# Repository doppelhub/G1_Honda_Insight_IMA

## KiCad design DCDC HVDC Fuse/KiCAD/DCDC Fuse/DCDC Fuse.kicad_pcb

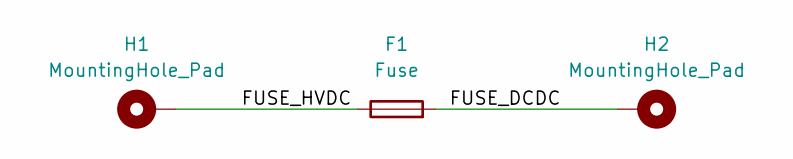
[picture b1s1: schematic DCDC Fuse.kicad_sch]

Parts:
F1: Fuse; Fuseholder_Cylinder-5x20mm_Schurter_0031_8201_Horizontal_Op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
H1, H2: MountingHole_Pad; MountingHole_8.4mm_M8_Pad_TopBottom

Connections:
/FUSE_DCDC: F1.2, H2.1
/FUSE_HVDC: F1.1, H1.1

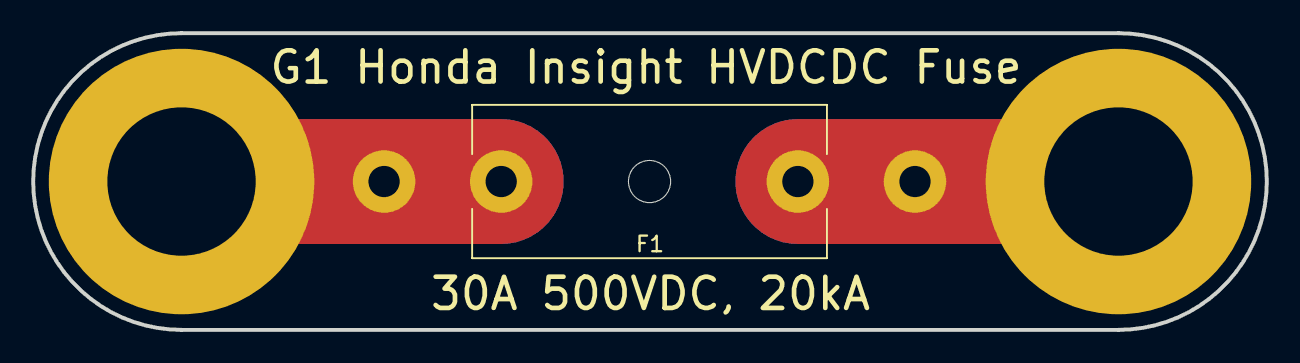
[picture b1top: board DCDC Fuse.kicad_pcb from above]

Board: 2 copper layers, 79.0 x 19.0 mm, 3 parts (0 on the bottom side), 2 nets.

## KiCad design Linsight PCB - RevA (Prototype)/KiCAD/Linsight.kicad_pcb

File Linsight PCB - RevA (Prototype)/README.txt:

THIS IS A PROTOTYPE!!
THIS IS NOT A FINISHED PRODUCT!
DO NOT MAKE THIS PCB AND EXPECT IT TO WORK.

See Folder "RevA Issues" for known issues.

This is a framework ONLY.  Further engineering effort required.

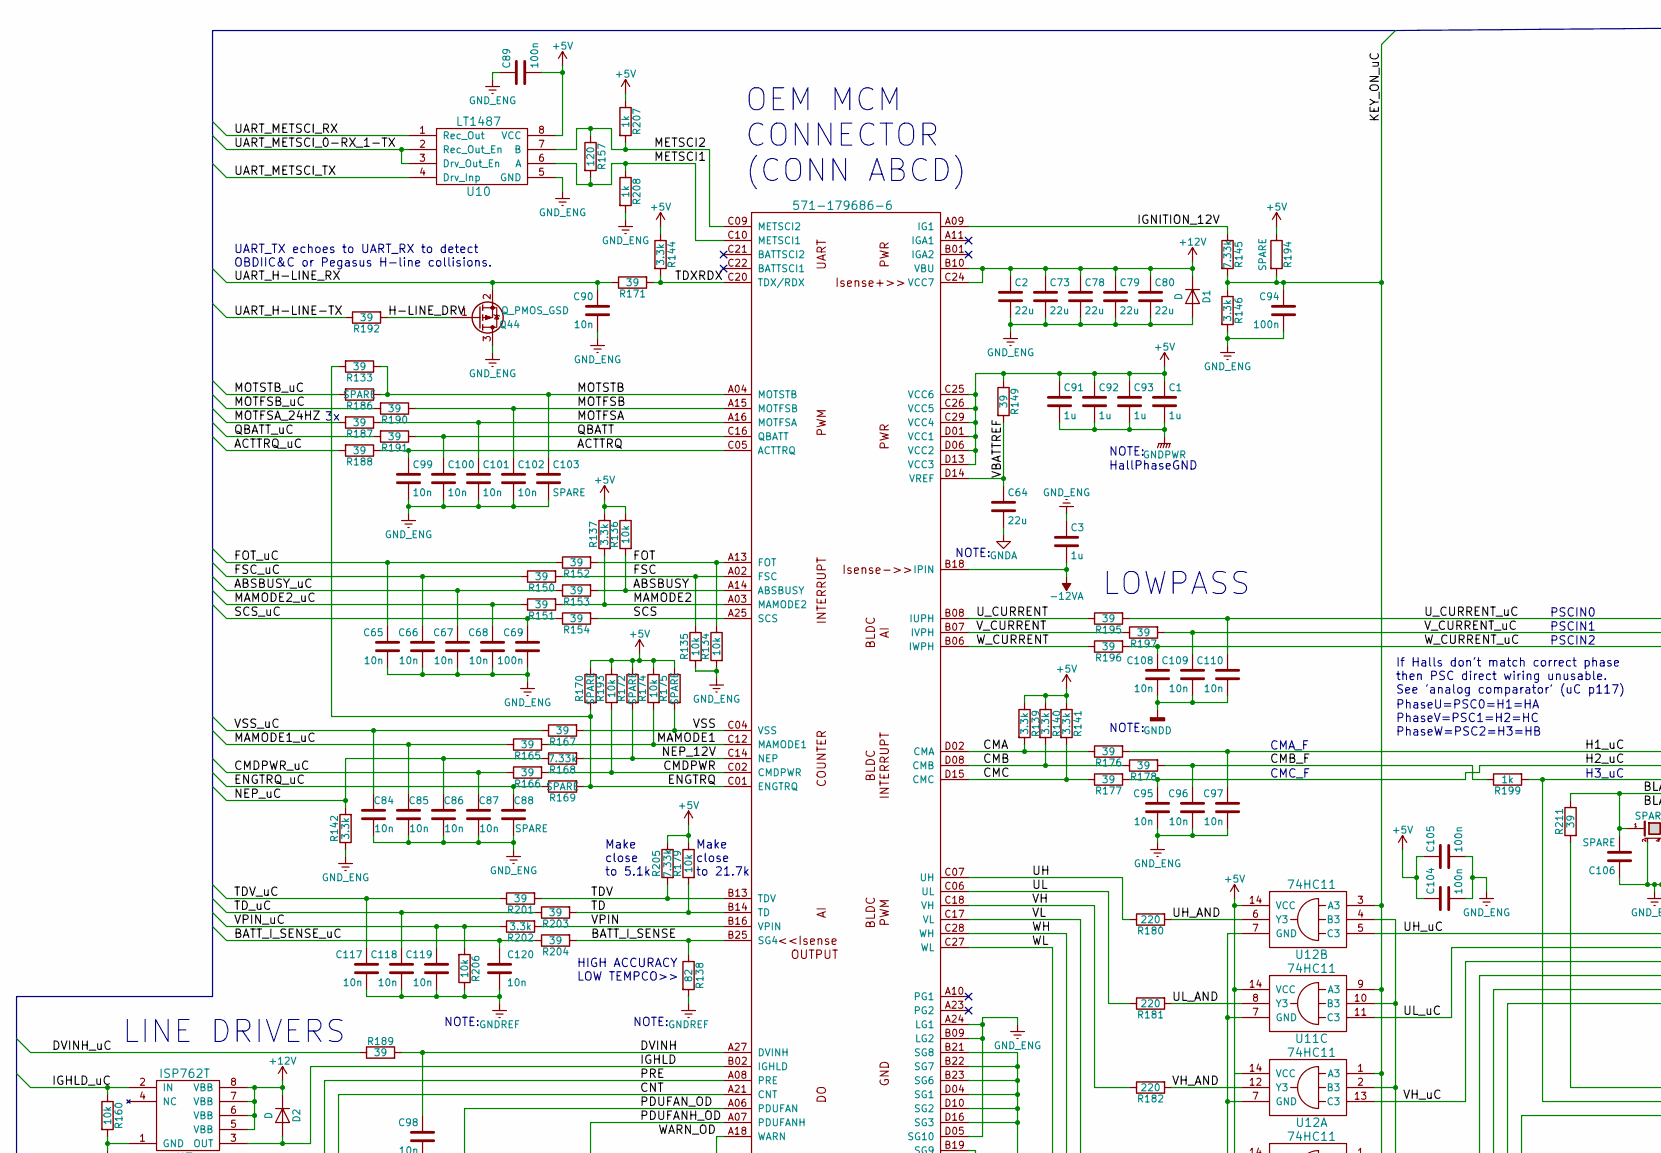
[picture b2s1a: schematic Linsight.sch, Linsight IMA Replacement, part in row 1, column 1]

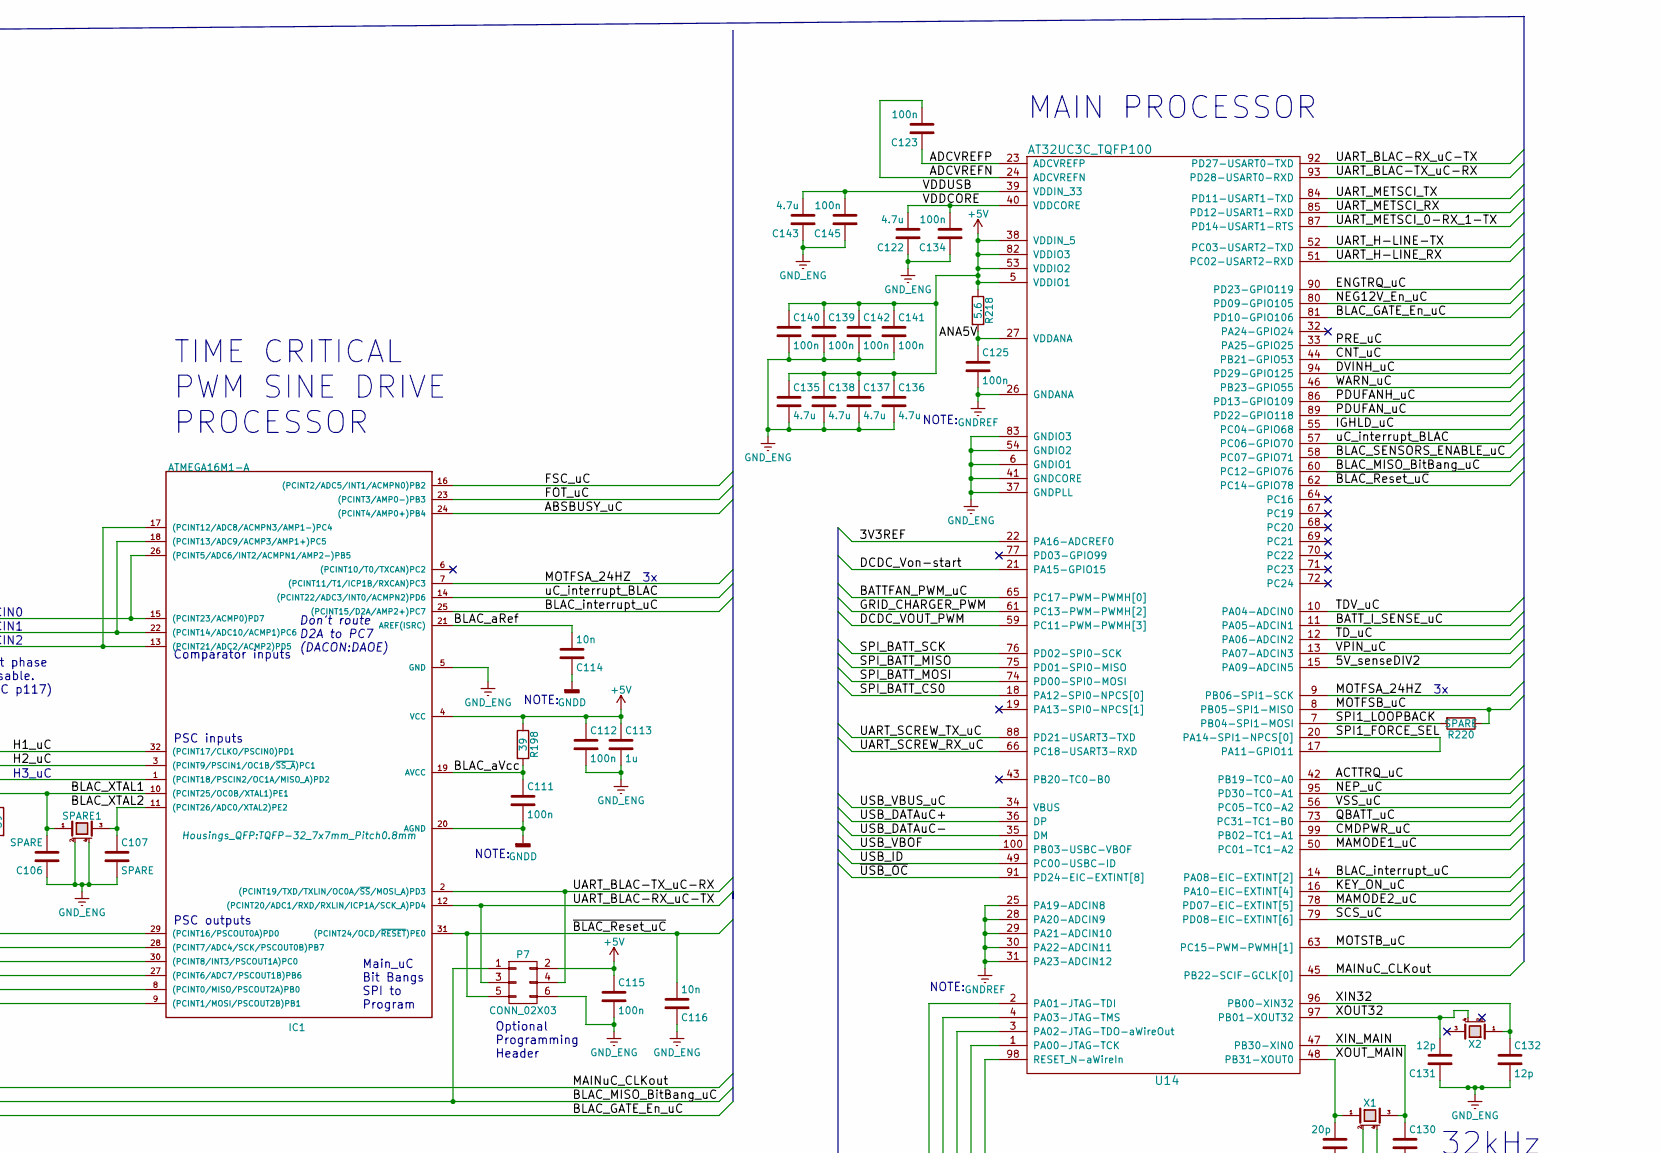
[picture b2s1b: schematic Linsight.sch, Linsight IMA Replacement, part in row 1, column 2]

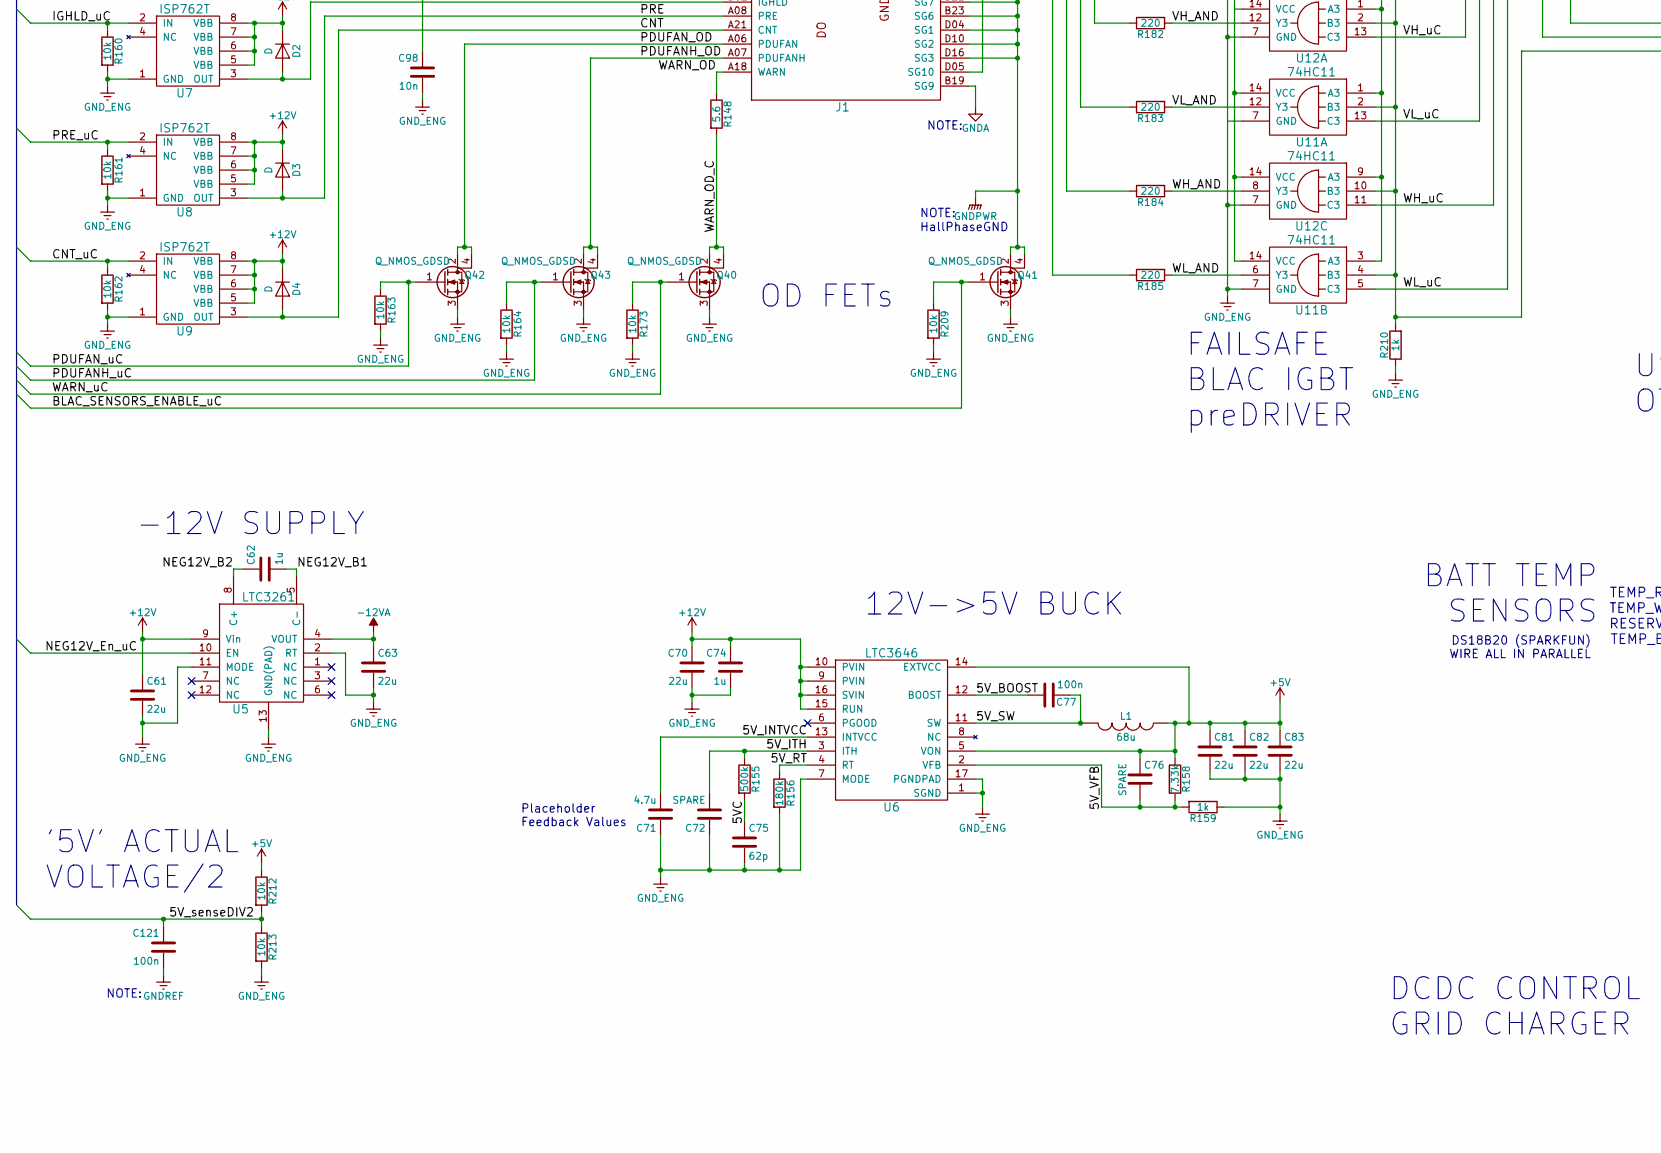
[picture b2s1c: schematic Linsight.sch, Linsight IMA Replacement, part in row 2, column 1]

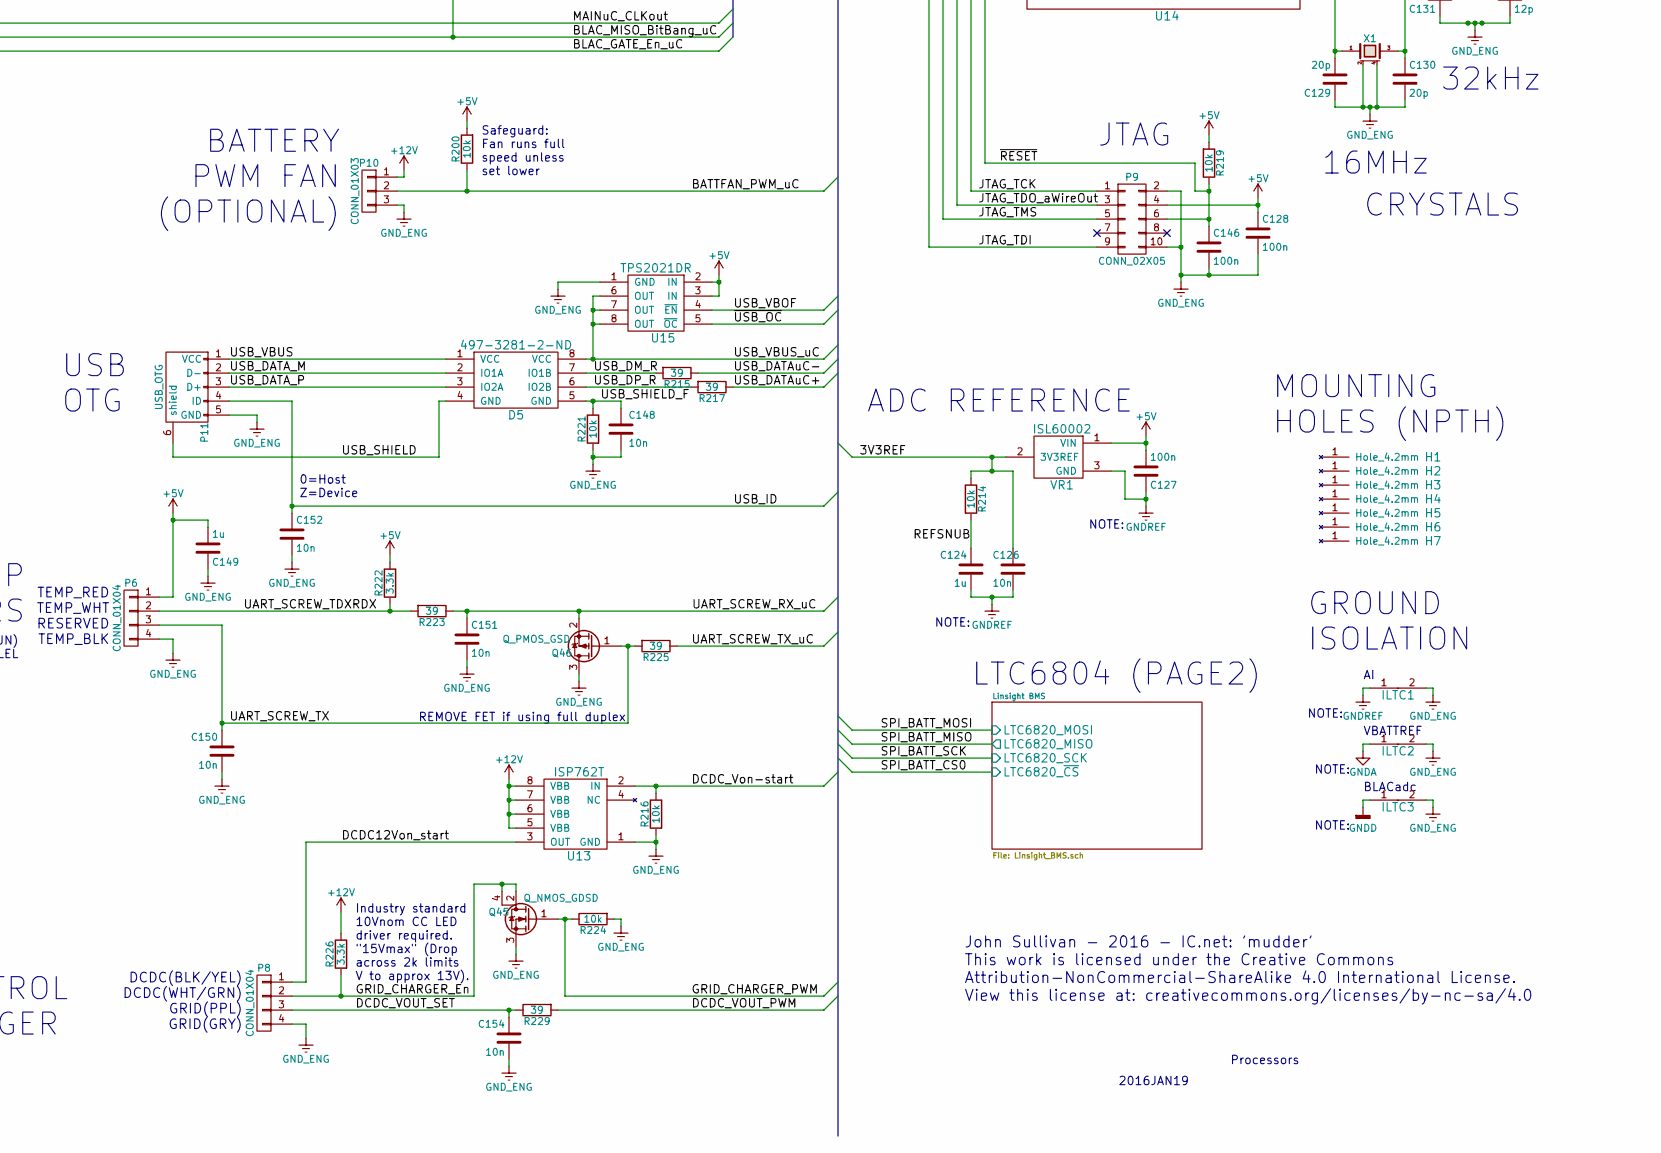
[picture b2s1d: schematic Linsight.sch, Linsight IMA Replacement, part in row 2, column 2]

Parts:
C1, C3, C62, C74, C91, C92, C93, C113, C124, C149: 1u; C_0805
C2, C61, C63, C64, C70, C73, C78, C79, C80, C81, C82, C83: 22u; C_1210
C65, C66, C67, C68, C84, C85, C86, C87, C90, C95, C96, C97, C98, C99, C100, C101, C102, C108, C109, C110, C114, C116, C117, C118, C119, C120, C126, C148, C150, C151, C152, C154: 10n; C_0805
C69, C77, C89, C94, C104, C105, C111, C112, C115, C121, C123, C125, C127, C128, C134, C139, C140, C141, C142, C145, C146: 100n; C_0805
C71, C122, C135, C136, C137, C138, C143: 4.7u; C_0805
C72, C76, C88, C103, C106, C107: SPARE; C_0805
C75: 62p; C_0805
C129, C130: 20p; C_0805
C131, C132: 12p; C_0805
D1: D; SMBJ16AFSTR-ND; digikey SMBJ16AFSTR-ND
D2, D3, D4: D; SOT-23; digikey BAT54-FDITR-ND
D5: 497-3281-2-ND; SOIC-8-N; digikey 497-3281-2-nd
H1, H2, H3, H4, H5, H6, H7: Hole-4mm2; TH_4mm2
IC1: ATMEGA16M1-A; TQFP-32_7x7mm_Pitch0.8mm
ILTC1, ILTC2, ILTC3: ILTC
J1: 571-179686-6
L1: 68u; 445-1987-2-ND
P6, P8: CONN_01X04; 277-5744-ND
P7: CONN_02X03; Pin_Header_Straight_2x03
P9: CONN_02X05; Pin_Header_Straight_2x05
P10: CONN_01X03; 277-5749-ND; Digikey 277-5749-ND
P11: USB_OTG; USB_WM17120-ND; Digikey WM2072-ND
Q40, Q41, Q42, Q43, Q45: Q_NMOS_GDSD; SOT89; Digikey ZXMN3A01ZTADITR-ND
Q44, Q46: Q_PMOS_GSD; SOT-23
R133, R149, R150, R151, R152, R153, R154, R165, R166, R167, R171, R176, R177, R178, R187, R188, R189, R190, R191, R192, R195, R196, R197, R198, R201, R203, R204, R211, R215, R217, R223, R225, R229: 39; R_0805
R134, R135, R136, R160, R161, R162, R163, R164, R173, R174, R179, R193, R200, R206, R209, R212, R213, R214, R216, R219, R221, R224: 10k; R_0805
R137, R139, R140, R141, R142, R144, R146, R202, R222, R226: 3.3k; R_0805
R138: 82; R_0805
R145, R158, R168, R205: 7.33k; R_0805
R148, R218: 5.6; R_1206
R155: 500k; R_0805
R156: 180k; R_0805
R157: 120; R_0805
R159, R199, R207, R208, R210: 1k; R_0805
R169, R170, R172, R175, R186, R194, R220: SPARE; R_0805
R180, R181, R182, R183, R184, R185: 220; R_0805
SPARE1: CRYSTAL_SMD_4pin; XC1513TR-ND
U5: LTC3261
U6: LTC3646
U7: ISP762T; Digikey ISP762TTR-ND
U8, U9, U13: ISP762T
U10: LT1487; SOIC-8-N
U11, U12: 74HC11; SOIC-14
U14: AT32UC3C_TQFP100; TQFP-100_14x14mm_Pitch0.5mm
U15: TPS2021DR; SOIC-8-N; Digikey TPS2021DR
VR1: ISL60002; SOT-23; Digikey ISL60002DAH333Z-TKTR-ND
X1: CRYSTAL_SMD_4pin; XC1513TR-ND
X2: CRYSTAL_SMD_4pin; 32kosc_535-10242-2-nd; digikey 535-10242-2-nd

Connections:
+5V: C1.1, C76.1, C81.1, C82.1, C83.1, C89.2, C91.1, C92.1, C93.1, C104.1, C105.1, C112.1, C113.1, C115.1, C127.2, C128.1, C135.1, C136.1, C137.1, C138.1, C139.1, C140.1, C141.1, C142.1, C149.2, IC1.4 (VCC), J1.C25 (VCC6), J1.C26 (VCC5), J1.C29 (VCC4), J1.D01 (VCC1), J1.D06 (VCC2), J1.D13 (VCC3), L1.1, P6.1, P7.2, P9.4, R136.1, R137.1, R139.1, R140.1, R141.1, R144.1, R149.1, R158.1, R170.1, R172.1, R174.1, R175.1, R179.1, R193.1, R194.1, R198.1, R200.2, R205.1, R207.1, R212.1, R218.1, R219.2, R222.1, U6.5 (VON), U6.14 (EXTVCC), U10.8 (VCC), U11.14 (VCC), U12.14 (VCC), U14.5 (VDDIO1), U14.38 (VDDIN_5), U14.53 (VDDIO2), U14.82 (VDDIO3), U15.2 (IN), U15.3 (IN), VR1.1 (VIN); also elsewhere on the board
+12V: C2.1, C61.1, C70.1, C73.1, C74.1, C78.1, C79.1, C80.1, D1.1 (K), D2.1 (K), D3.1 (K), D4.1 (K), J1.B10 (VBU), J1.C24 (VCC7), P10.1, R226.1, U5.9 (Vin), U6.9 (PVIN), U6.10 (PVIN), U6.15 (RUN), U6.16 (SVIN), U7.5 (VBB), U7.6 (VBB), U7.7 (VBB), U7.8 (VBB), U8.5 (VBB), U8.6 (VBB), U8.7 (VBB), U8.8 (VBB), U9.5 (VBB), U9.6 (VBB), U9.7 (VBB), U9.8 (VBB), U13.5 (VBB), U13.6 (VBB), U13.7 (VBB), U13.8 (VBB)
-12VA: C3.2, C63.1, J1.B18 (IPIN), U5.4 (VOUT)
/3V3REF: C126.1, R214.1, U14.22 (PA16-ADCREF0), VR1.2 (3V3REF)
/5VC: C75.1, R155.2
/5V_BOOST: C77.1, U6.12 (BOOST)
/5V_INTVCC: C71.2, U6.13 (INTVCC)
/5V_ITH: C72.2, R155.1, U6.3 (ITH)
/5V_RT: R156.1, U6.4 (RT)
/5V_SW: C77.2, L1.2, U6.11 (SW)
/5V_VFB: C76.2, R158.2, R159.2, U6.2 (VFB)
/5V_senseDIV2: C121.1, R212.2, R213.1, U14.15 (PA09-ADCIN5)
/ABSBUSY: J1.A14 (ABSBUSY), R136.2, R153.2
/ABSBUSY_uC: C67.1, IC1.24 ((PCINT4/AMP0+)PB4), R153.1
/ACTTRQ: C99.1, J1.C05 (ACTTRQ), R188.1
/ACTTRQ_uC: R188.2, U14.42 (PB19-TC0-A0)
/ADCVREFN: C123.2, U14.24 (ADCVREFN)
/ADCVREFP: C123.1, U14.23 (ADCVREFP)
/ANA5V: C125.1, R218.2, U14.27 (VDDANA)
/BATTFAN_PWM_uC: P10.2, R200.1, U14.65 (PC17-PWM-PWMH[0])
/BATT_I_SENSE: J1.B25 (SG4), R138.1, R204.2
/BATT_I_SENSE_uC: C120.2, R204.1, U14.11 (PA05-ADCIN1)
/BLAC_GATE_En_uC: R210.2, U11.2 (B3), U11.4 (B3), U11.10 (B3), U12.2 (B3), U12.4 (B3), U12.10 (B3), U14.81 (PD10-GPIO106)
/BLAC_MISO_BitBang_uC: IC1.1 ((PCINT18/PSCIN2/OC1A/MISO_A)PD2), P7.1, R199.2, U14.60 (PC12-GPIO76)
/BLAC_SENSORS_ENABLE_uC: Q41.1 (G), R209.1, U14.58 (PC07-GPIO71)
/BLAC_XTAL1: C106.2, IC1.10 ((PCINT25/OC0B/XTAL1)PE1), R211.1, SPARE1.1
/BLAC_XTAL2: C107.1, IC1.11 ((PCINT26/ADC0/XTAL2)PE2), SPARE1.3
/BLAC_aRef: C114.2, IC1.21 (AREF(ISRC))
/BLAC_aVcc: C111.1, IC1.19 (AVCC), R198.2
/BLAC_interrupt_uC: IC1.25 ((PCINT15/D2A/AMP2+)PC7), U14.14 (PA08-EIC-EXTINT[2])
/CMA: J1.D02 (CMA), R139.2, R176.1
/CMB: J1.D08 (CMB), R140.2, R178.1
/CMB_F: C96.1, R178.2, R199.1
/CMC: J1.D15 (CMC), R141.2, R177.1
/CMDPWR: J1.C02 (CMDPWR), R166.2, R193.2
/CMDPWR_uC: C87.1, R166.1, U14.99 (PB02-TC1-A1)
/CNT: D4.2 (A), J1.A21 (CNT), U9.3 (OUT)
/CNT_uC: R162.1, U9.2 (IN), U14.44 (PB21-GPIO53)
/DCDC12Von_start: P8.1, U13.3 (OUT)
/DCDC_VOUT_PWM: R229.2, U14.59 (PC11-PWM-PWMH[3])
/DCDC_VOUT_SET: C154.1, P8.3, R229.1
/DCDC_Von-start: R216.1, U13.2 (IN), U14.21 (PA15-GPIO15)
/DVINH: C98.1, J1.A27 (DVINH), R189.2
/DVINH_uC: R189.1, U14.94 (PD29-GPIO125)
/ENGTRQ: J1.C01 (ENGTRQ), R133.2, R169.2, R170.2
/ENGTRQ_uC: C88.1, R169.1, U14.90 (PD23-GPIO119)
/FOT: J1.A13 (FOT), R134.1, R152.2
/FOT_uC: C65.1, IC1.23 ((PCINT3/AMP0-)PB3), R152.1
/FSC: J1.A02 (FSC), R135.1, R150.2
/FSC_uC: C66.1, IC1.16 ((PCINT2/ADC5/INT1/ACMPN0)PB2), R150.1
/GRID_CHARGER_En: P8.2, Q45.2 (D), Q45.4 (D), R226.2
/GRID_CHARGER_PWM: Q45.1 (G), R224.1, U14.61 (PC13-PWM-PWMH[2])
/H1_uC: C97.1, IC1.32 ((PCINT17/CLKO/PSCIN0)PD1), R176.2
/H2_uC: C95.1, IC1.3 ((PCINT9/PSCIN1/OC1B/~SS_A~)PC1), R177.2
/H-LINE_DRV: Q44.1 (G), R192.2
/IGHLD: D2.2 (A), J1.B02 (IGHLD), U7.3 (OUT)
/IGHLD_uC: R160.1, U7.2 (IN), U14.55 (PC04-GPIO68)
/IGNITION_12V: J1.A09 (IG1), R145.1
/JTAG_TCK: P9.1, U14.1 (PA00-JTAG-TCK)
/JTAG_TDI: P9.9, U14.2 (PA01-JTAG-TDI)
/JTAG_TDO_aWireOut: P9.3, U14.3 (PA02-JTAG-TDO-aWireOut)
/JTAG_TMS: P9.5, U14.4 (PA03-JTAG-TMS)
/KEY_ON_uC: C94.1, R145.2, R146.1, R194.2, U11.1 (A3), U11.3 (A3), U11.9 (A3), U12.1 (A3), U12.3 (A3), U12.9 (A3), U14.16 (PA10-EIC-EXTINT[4])
/Linsight BMS/LTC6820_MISO: U14.75 (PD01-SPI0-MISO); also elsewhere on the board
/Linsight BMS/LTC6820_MOSI: U14.74 (PD00-SPI0-MOSI); also elsewhere on the board
/Linsight BMS/LTC6820_SCK: U14.76 (PD02-SPI0-SCK); also elsewhere on the board
/Linsight BMS/LTC6820_~CS: U14.18 (PA12-SPI0-NPCS[0]); also elsewhere on the board
/MAINuC_CLKout: R211.2, U14.45 (PB22-SCIF-GCLK[0])
/MAMODE1: J1.C12 (MAMODE1), R165.2, R174.2
/MAMODE1_uC: C85.1, R165.1, U14.50 (PC01-TC1-A2)
/MAMODE2: J1.A03 (MAMODE2), R137.2, R151.2
/MAMODE2_uC: C68.1, R151.1, U14.78 (PD07-EIC-EXTINT[5])
/METSCI1: J1.C10 (METSCI1), R157.2, R208.1, U10.6 (A)
/METSCI2: J1.C09 (METSCI2), R157.1, R207.2, U10.7 (B)
/MOTFSA: C101.1, J1.A16 (MOTFSA), R187.1
/MOTFSA_24HZ: IC1.7 ((PCINT11/T1/ICP1B/RXCAN)PC3), R187.2, U14.9 (PB06-SPI1-SCK)
/MOTFSB: C102.1, J1.A15 (MOTFSB), R190.1
/MOTFSB_uC: R190.2, R220.1, U14.8 (PB05-SPI1-MISO)
/MOTSTB: C103.1, J1.A04 (MOTSTB), R133.1, R186.1
/MOTSTB_uC: R186.2, U14.63 (PC15-PWM-PWMH[1])
/NEG12V_B1: C62.2, U5.5 (C-)
/NEG12V_B2: C62.1, U5.8 (C+)
/NEG12V_En_uC: U5.10 (EN), U14.80 (PD09-GPIO105)
/NEP_12V: J1.C14 (NEP), R168.2, R172.2
/NEP_uC: C86.1, R142.2, R168.1, U14.95 (PD30-TC0-A1)
/PDUFANH_OD: J1.A07 (PDUFANH), Q43.2 (D), Q43.4 (D)
/PDUFANH_uC: Q43.1 (G), R164.1, U14.86 (PD13-GPIO109)
/PDUFAN_OD: J1.A06 (PDUFAN), Q42.2 (D), Q42.4 (D)
/PDUFAN_uC: Q42.1 (G), R163.1, U14.89 (PD22-GPIO118)
/PRE: D3.2 (A), J1.A08 (PRE), U8.3 (OUT)
/PRE_uC: R161.1, U8.2 (IN), U14.33 (PA25-GPIO25)
/QBATT: C100.1, J1.C16 (QBATT), R191.1
/QBATT_uC: R191.2, U14.73 (PC31-TC1-B0)
/REFSNUB: C124.1, R214.2
/SCS: J1.A25 (SCS), R154.2
/SCS_uC: C69.1, R154.1, U14.79 (PD08-EIC-EXTINT[6])
/SPI1_FORCE_SEL: U14.17 (PA11-GPIO11), U14.20 (PA14-SPI1-NPCS[0])
/SPI1_LOOPBACK: R220.2, U14.7 (PB04-SPI1-MOSI)
/TD: J1.B14 (TD), R179.2, R203.2
/TDV: J1.B13 (TDV), R201.2, R205.2
/TDV_uC: C117.1, R201.1, U14.10 (PA04-ADCIN0)
/TDXRDX: J1.C20 (TDX/RDX), R144.2, R171.2
/TD_uC: C118.1, R203.1, U14.12 (PA06-ADCIN2)
/UART_BLAC-RX_uC-TX: IC1.12 ((PCINT20/ADC1/RXD/RXLIN/ICP1A/SCK_A)PD4), P7.3, U14.92 (PD27-USART0-TXD)
/UART_BLAC-TX_uC-RX: IC1.2 ((PCINT19/TXD/TXLIN/OC0A/~SS~/MOSI_A)PD3), P7.4, U14.93 (PD28-USART0-RXD)
/UART_H-LINE-TX: R192.1, U14.52 (PC03-USART2-TXD)
/UART_H-LINE_RX: C90.1, Q44.2 (S), R171.1, U14.51 (PC02-USART2-RXD)
/UART_METSCI_0-RX_1-TX: U10.2 (Rec_Out_En), U10.3 (Drv_Out_En), U14.87 (PD14-USART1-RTS)
/UART_METSCI_RX: U10.1 (Rec_Out), U14.85 (PD12-USART1-RXD)
/UART_METSCI_TX: U10.4 (Drv_Inp), U14.84 (PD11-USART1-TXD)
/UART_SCREW_RX_uC: C151.1, Q46.2 (S), R223.1, U14.66 (PC18-USART3-RXD)
/UART_SCREW_TDXRDX: P6.2, R222.2, R223.2
/UART_SCREW_TX: C150.1, P6.3, Q46.1 (G), R225.2
/UART_SCREW_TX_uC: R225.1, U14.88 (PD21-USART3-TXD)
/UH: J1.C07 (UH), R180.1
/UH_AND: R180.2, U12.6 (Y3)
/UH_uC: IC1.29 ((PCINT16/PSCOUT0A)PD0), U12.5 (C3)
/UL: J1.C06 (UL), R181.1
/UL_AND: R181.2, U11.8 (Y3)
/UL_uC: IC1.28 ((PCINT7/ADC4/SCK/PSCOUT0B)PB7), U11.11 (C3)
/USB_DATA_M: D5.2 (IO1A), P11.2 (D-)
/USB_DATA_P: D5.3 (IO2A), P11.3 (D+)
/USB_DATAuC+: R217.1, U14.36 (DP)
/USB_DATAuC-: R215.1, U14.35 (DM)
/USB_DM_R: D5.7 (IO1B), R215.2
/USB_DP_R: D5.6 (IO2B), R217.2
/USB_ID: C152.1, P11.4 (ID), U14.49 (PC00-USBC-ID)
/USB_SHIELD: D5.4 (GND), P11.6 (shield)
/USB_SHIELD_F: C148.2, D5.5 (GND), R221.1
/USB_VBOF: U14.100 (PB03-USBC-VBOF), U15.4 (~EN)
/USB_VBUS: D5.1 (VCC), P11.1 (VCC)
/USB_VBUS_uC: D5.8 (VCC), U14.34 (VBUS), U15.6 (OUT), U15.7 (OUT), U15.8 (OUT)
/U_CURRENT: J1.B08 (IUPH), R195.1
/U_CURRENT_uC: C110.1, IC1.15 ((PCINT23/ACMP0)PD7), IC1.26 ((PCINT5/ADC6/INT2/ACMPN1/AMP2-)PB5), R195.2
/VBATTREF: C64.1, J1.D14 (VREF), R149.2
/VDDCORE: C122.2, C134.2, U14.40 (VDDCORE)
/VDDUSB: C143.2, C145.2, U14.39 (VDDIN_33)
/VH: J1.C18 (VH), R182.1
/VH_AND: R182.2, U12.12 (Y3)
/VH_uC: IC1.30 ((PCINT8/INT3/PSCOUT1A)PC0), U12.13 (C3)
/VL: J1.C17 (VL), R183.1
/VL_AND: R183.2, U11.12 (Y3)
/VL_uC: IC1.27 ((PCINT6/ADC7/PSCOUT1B)PB6), U11.13 (C3)
/VPIN: J1.B16 (VPIN), R202.2
/VPIN_uC: C119.1, R202.1, R206.2, U14.13 (PA07-ADCIN3)
/VSS: J1.C04 (VSS), R167.2, R175.2
/VSS_uC: C84.1, R167.1, U14.56 (PC05-TC0-A2)
/V_CURRENT: J1.B07 (IVPH), R197.1
/V_CURRENT_uC: C109.1, IC1.18 ((PCINT13/ADC9/ACMP3/AMP1+)PC5), IC1.22 ((PCINT14/ADC10/ACMP1)PC6), R197.2
/WARN_OD: J1.A18 (WARN), R148.1
/WARN_OD_C: Q40.2 (D), Q40.4 (D), R148.2
/WARN_uC: Q40.1 (G), R173.1, U14.46 (PB23-GPIO55)
/WH: J1.C28 (WH), R184.1
/WH_AND: R184.2, U12.8 (Y3)
/WH_uC: IC1.8 ((PCINT0/MISO/PSCOUT2A)PB0), U12.11 (C3)
/WL: J1.C27 (WL), R185.1
/WL_AND: R185.2, U11.6 (Y3)
/WL_uC: IC1.9 ((PCINT1/MOSI/PSCOUT2B)PB1), U11.5 (C3)
/W_CURRENT: J1.B06 (IWPH), R196.1
/W_CURRENT_uC: C108.1, IC1.13 ((PCINT21/ADC2/ACMP2)PD5), IC1.17 ((PCINT12/ADC8/ACMPN3/AMP1-)PC4), R196.2
/XIN32: C132.1, U14.96 (PB00-XIN32), X2.1
/XIN_MAIN: C130.1, U14.47 (PB30-XIN0), X1.3
/XOUT32: C131.2, U14.97 (PB01-XOUT32), X2.4 (case)
/XOUT_MAIN: C129.2, U14.48 (PB31-XOUT0), X1.1
/uC_interrupt_BLAC: IC1.14 ((PCINT22/ADC3/INT0/ACMPN2)PD6), U14.57 (PC06-GPIO70)
/~BLAC_Reset_uC: C116.2, IC1.31 ((PCINT24/OCD/~RESET~)PE0), P7.5, U14.62 (PC14-GPIO78)
/~RESET: C146.1, P9.6, R219.1, U14.98 (RESET_N-aWireIn)
/~USB_OC: U14.91 (PD24-EIC-EXTINT[8]), U15.5 (~OC)
GNDA: C64.2, ILTC2.1, J1.B19 (SG9)
GNDD: C108.2, C109.2, C110.2, C111.2, C114.1, IC1.20 (AGND), ILTC3.1
GNDPWR: C1.2, C91.2, C92.2, C93.2, J1.B21 (SG8), J1.B22 (SG7), J1.B23 (SG6), J1.D04 (SG1), J1.D10 (SG2), J1.D16 (SG3), Q41.2 (D), Q41.4 (D)
GNDREF: C117.2, C118.2, C119.2, C120.1, C121.2, C124.2, C125.2, C126.2, C127.1, ILTC1.1, R138.2, R206.1, U14.25 (PA19-ADCIN8), U14.26 (GNDANA), U14.28 (PA20-ADCIN9), U14.29 (PA21-ADCIN10), U14.30 (PA22-ADCIN11), U14.31 (PA23-ADCIN12), VR1.3 (GND)
GND_ENG: C2.2, C3.1, C61.2, C63.2, C65.2, C66.2, C67.2, C68.2, C69.2, C70.2, C71.1, C72.1, C73.2, C74.2, C75.2, C78.2, C79.2, C80.2, C81.2, C82.2, C83.2, C84.2, C85.2, C86.2, C87.2, C88.2, C89.1, C90.2, C94.2, C95.2, C96.2, C97.2, C98.2, C99.2, C100.2, C101.2, C102.2, C103.2, C104.2, C105.2, C106.1, C107.2, C112.2, C113.2, C115.2, C116.1, C122.1, C128.2, C129.1, C130.2, C131.1, C132.2, C134.1, C135.2, C136.2, C137.2, C138.2, C139.2, C140.2, C141.2, C142.2, C143.1, C145.1, C146.2, C148.1, C149.1, C150.2, C151.2, C152.2, C154.2, D1.2 (A), IC1.5 (GND), ILTC1.2, ILTC2.2, ILTC3.2, J1.A24 (LG1), J1.B09 (LG2), J1.D05 (SG10), P6.4, P7.6, P8.4, P9.2, P9.10, P10.3, P11.5 (GND), Q40.3 (S), Q41.3 (S), Q42.3 (S), Q43.3 (S), Q44.3 (D), Q45.3 (S), Q46.3 (D), R134.2, R135.2, R142.1, R146.2, R156.2, R159.1, R160.2, R161.2, R162.2, R163.2, R164.2, R173.2, R208.2, R209.2, R210.1, R213.2, R216.2, R221.2, R224.2, SPARE1.2 (case), SPARE1.4 (case), U5.2 (RT), U5.11 (MODE), U5.13 (GND(PAD)), U6.1 (SGND), U6.7 (MODE), U6.17 (PGNDPAD), U7.1 (GND), U8.1 (GND), U9.1 (GND), U10.5 (GND), U11.7 (GND), U12.7 (GND), U13.1 (GND), U14.6 (GNDIO1), U14.37 (GNDPLL), U14.41 (GNDCORE), U14.54 (GNDIO2), U14.83 (GNDIO3), U15.1 (GND), X1.2 (case), X1.4 (case); also elsewhere on the board

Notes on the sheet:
HIGH ACCURACY LOW TEMPCO>>
Don't route D2A to PC7 (DACON:DAOE)
Comparator inputs
PSC inputs
PhaseU=PSC0=H1=HA PhaseV=PSC1=H2=HC PhaseW=PSC2=H3=HB
If Halls don't match correct phase then PSC direct wiring unusable. See 'analog comparator' (uC p117)
Placeholder Feedback Values
Optional Programming Header
Main_uC Bit Bangs SPI to Program
Make close to 5.1k
PSCIN0
PSCIN1
PSCIN2
Safeguard: Fan runs full speed unless set lower
NOTE:
VBATTREF
PSC outputs
BLACadc
UART_TX echoes to UART_RX to detect OBDIIC&C or Pegasus H-line collisions.
0=Host Z=Device
REMOVE FET if using full duplex
DS18B20 (SPARKFUN) WIRE ALL IN PARALLEL
LTC6804 (PAGE2)
MAIN PROCESSOR
12V->5V BUCK
-12V SUPPLY
'5V' ACTUAL VOLTAGE/2
BATTERY PWM FAN (OPTIONAL)
USB OTG
BATT TEMP SENSORS
TIME CRITICAL PWM SINE DRIVE PROCESSOR
OEM MCM CONNECTOR (CONN ABCD)
ADC REFERENCE
JTAG
MOUNTING HOLES (NPTH)
GROUND ISOLATION
16MHz
32kHz
CRYSTALS
FAILSAFE BLAC IGBT preDRIVER
